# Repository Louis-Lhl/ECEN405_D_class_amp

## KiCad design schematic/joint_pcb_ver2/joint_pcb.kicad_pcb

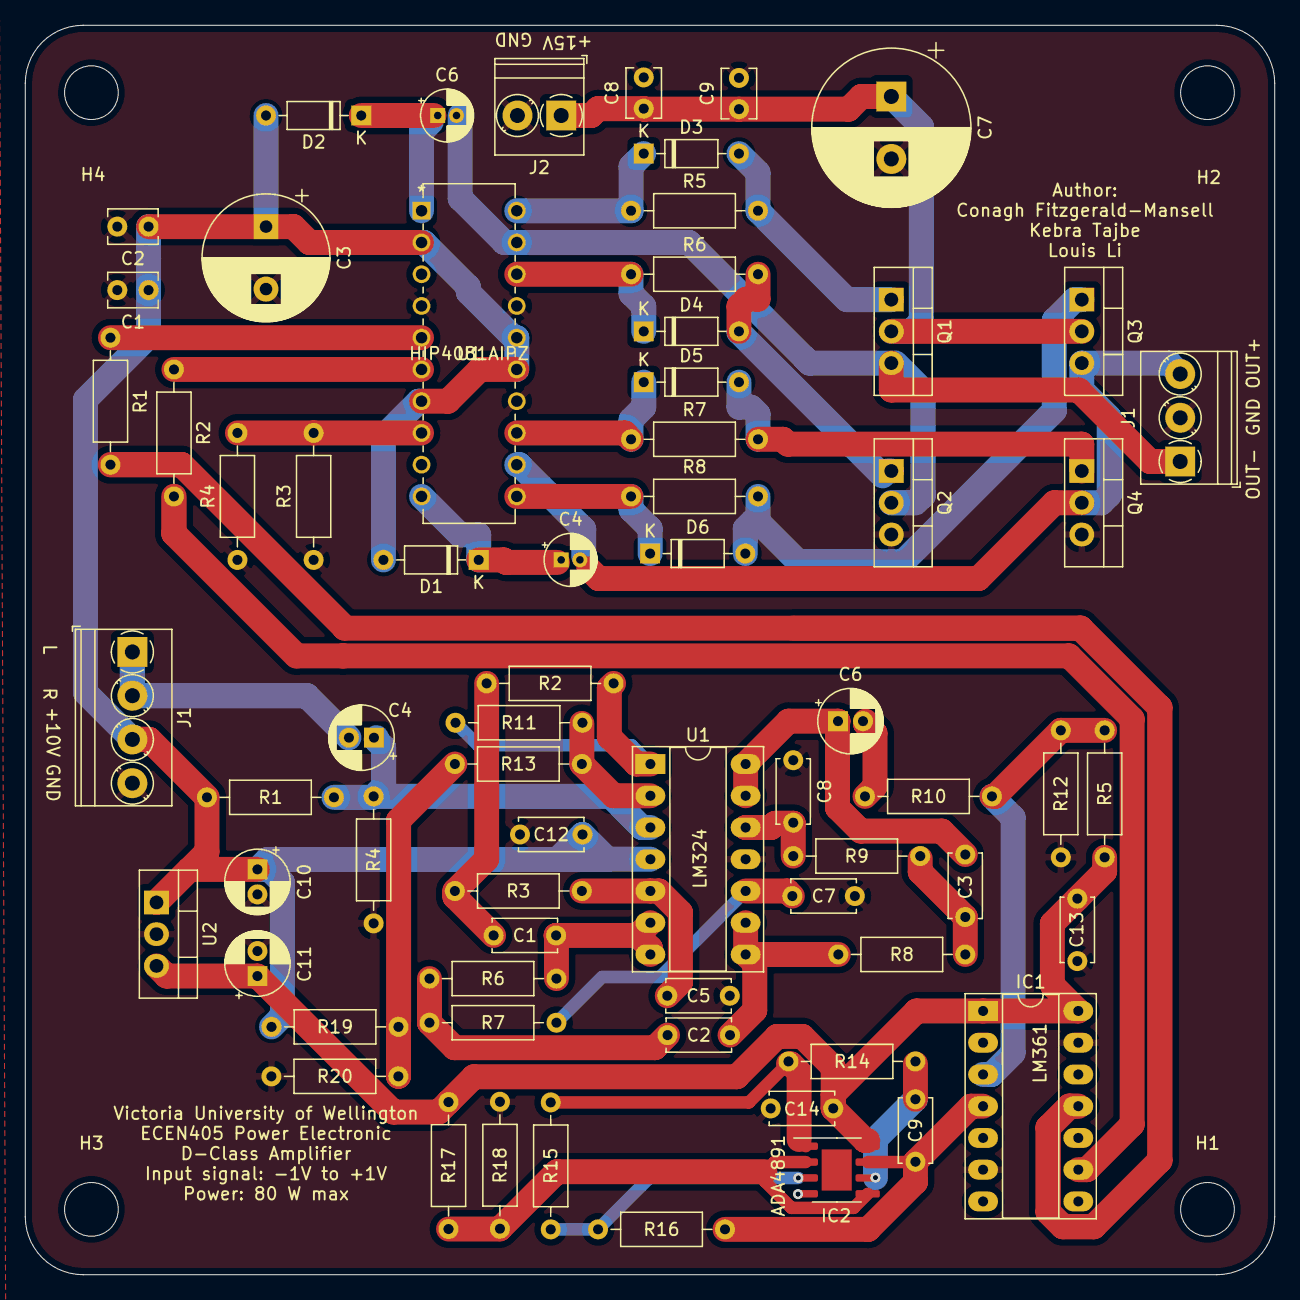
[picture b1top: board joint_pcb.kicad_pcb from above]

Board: 2 copper layers, 100.0 x 100.0 mm, 72 parts (0 on the bottom side), 41 nets.

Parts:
C1: 47n; C_Disc_D5.0mm_W2.5mm_P5.00mm
C1#2, C8#2: 10uF; C_Disc_D3.8mm_W2.6mm_P2.50mm
C2, C3: 56n; C_Disc_D5.0mm_W2.5mm_P5.00mm
C2#2, C9#2: 0.1uF; C_Disc_D3.8mm_W2.6mm_P2.50mm
C3#2: 100uF; CP_Radial_D10.0mm_P5.00mm
C4, C6: 100u; CP_Radial_D5.0mm_P2.00mm
C4#2, C6#2: 1uF; CP_Radial_D4.0mm_P1.50mm
C5, C9: 4.7n; C_Disc_D5.0mm_W2.5mm_P5.00mm
C7, C8: 5.6n; C_Disc_D5.0mm_W2.5mm_P5.00mm
C7#2: 1000uF; CP_Radial_D12.5mm_P5.00mm
C10, C11: 10u; CP_Radial_D5.0mm_P2.00mm
C12, C13, C14: 100nF; C_Disc_D5.0mm_W2.5mm_P5.00mm
D1, D2, D3, D4, D5, D6: 1N4148; D_DO-35_SOD27_P7.62mm_Horizontal
H1, H2, H3, H4: MountingHole; MountingHole_4.3mm_M4
IC1: LM361N_NOPB; DIP-14_W7.62mm_Socket_LongPads
IC2: ADA4891-2ARMZ-R7; SOIC-8-1EP_3.9x4.9mm_P1.27mm_EP2.41x3.3mm
J1: Screw_Terminal_01x04; TerminalBlock_Phoenix_PT-1,5-4-3.5-H_1x04_P3.50mm_Horizontal
J1#2: Power_PWM_output; TerminalBlock_Phoenix_PT-1,5-3-3.5-H_1x03_P3.50mm_Horizontal
J2: Amp_power; TerminalBlock_Phoenix_PT-1,5-2-3.5-H_1x02_P3.50mm_Horizontal
Q1, Q2, Q3, Q4: IRF510PBF; TO-220-3_Vertical
R1, R5, R10, R12, R15, R17, R18, R19: 10k; R_Axial_DIN0207_L6.3mm_D2.5mm_P10.16mm_Horizontal
R1#2, R2#2: 470R; R_Axial_DIN0207_L6.3mm_D2.5mm_P10.16mm_Horizontal
R2, R13: 1.2k; R_Axial_DIN0207_L6.3mm_D2.5mm_P10.16mm_Horizontal
R3, R16: 8.2k; R_Axial_DIN0207_L6.3mm_D2.5mm_P10.16mm_Horizontal
R3#2, R4#2: 47kR; R_Axial_DIN0207_L6.3mm_D2.5mm_P10.16mm_Horizontal
R4, R14, R20: 1k; R_Axial_DIN0207_L6.3mm_D2.5mm_P10.16mm_Horizontal
R5#2, R6#2, R7#2, R8#2: 100R; R_Axial_DIN0207_L6.3mm_D2.5mm_P10.16mm_Horizontal
R6: 680; R_Axial_DIN0207_L6.3mm_D2.5mm_P10.16mm_Horizontal
R7: 15k; R_Axial_DIN0207_L6.3mm_D2.5mm_P10.16mm_Horizontal
R8: 560; R_Axial_DIN0207_L6.3mm_D2.5mm_P10.16mm_Horizontal
R9: 18k; R_Axial_DIN0207_L6.3mm_D2.5mm_P10.16mm_Horizontal
R11: 5.6k; R_Axial_DIN0207_L6.3mm_D2.5mm_P10.16mm_Horizontal
U1: LM324; DIP-14_W7.62mm_Socket_LongPads
U1#2: HIP4081AIPZ
U2: LM7805_TO220; TO-220-3_Vertical

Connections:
+5V: C11.1, C13.1, C14.1, IC1.1, IC1.14, IC2.8, R5.1, R17.1, U2.3
+15V: C7#2.1, C8#2.1, C9#2.1, J2.1, Q1.2, Q3.2
AHO: D6.1, R8#2.1, U1#2.11
AHS: C4#2.2, J1#2.3, Q3.3, Q4.2, U1#2.12
ALO: D5.1, R7#2.1, U1#2.13
BHO: D3.1, R5#2.1, U1#2.20
BHS: C6#2.2, J1#2.1, Q1.3, Q2.2, U1#2.19
BLO: D4.1, R6#2.1, U1#2.18
Bias: R13.1, R19.2, R20.1
GND: C1#2.2, C2#2.2, C3#2.2, C5.2, C7.1, C7#2.2, C8.1, C8#2.2, C9#2.2, C10.2, C11.2, C12.2, C13.2, C14.2, IC1.6, IC1.8, IC1.10, IC1.13, IC2.4, J1.4, J1#2.2, J2.2, Q2.3, Q4.3, R3#2.1, R4.2, R4#2.1, R12.2, R18.2, R20.2, U1.11, U1#2.4, U1#2.14, U1#2.17, U2.2
Input: C4.2, J1.1, J1.2
unnamed: C1.1, R6.2, U1.6, U1.7
unnamed: C1.2, R2.1, R3.2
unnamed: C2.1, R6.1, R7.2
unnamed: C2.2, R8.2, U1.8, U1.9
unnamed: C3.1, C6.1, U1.13, U1.14
unnamed: C3.2, R8.1, R9.2
unnamed: C4.1, C4#2.1, D1.1, R1.2, R4.1, U1.3, U1#2.10
unnamed: C5.1, R3.1, U1.5
unnamed: C6#2.1, D2.1, U1#2.1
unnamed: C6.2, R10.1
unnamed: C7.2, R7.1, U1.10
unnamed: C8.2, R9.1, U1.12
unnamed: C9.1, IC1.4, IC2.7, R16.1
unnamed: C9.2, IC2.6, R14.1
unnamed: D3.2, Q1.1, R5#2.2
unnamed: D4.2, Q2.1, R6#2.2
unnamed: D5.2, Q4.1, R7#2.2
unnamed: D6.2, Q3.1, R8#2.2
unnamed: IC2.1, R14.2, R15.2
unnamed: IC2.3, R15.1, R16.2
unnamed: R1#2.1, U1#2.5
unnamed: R2#2.1, U1#2.6
unnamed: R3#2.2, R4#2.2, U1#2.8
unnamed: R2.2, R11.1, U1.1
unnamed: R11.2, R13.2, U1.2
PWM+: IC1.11, R1#2.2
PWM-: IC1.9, R2#2.2
Vcc: C1#2.1, C2#2.1, C3#2.1, C10.1, C12.1, D1.2, D2.2, J1.3, R1.1, R19.1, U1.4, U1#2.2, U1#2.7, U1#2.15, U1#2.16, U2.1
Vref: IC2.2, IC2.5, R17.2, R18.1
filterOut: IC1.3, R5.2, R10.2, R12.1

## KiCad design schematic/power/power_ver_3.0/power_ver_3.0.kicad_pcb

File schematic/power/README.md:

# Schematic

This folder contains the schematic and PCB layout files and the PCB Gerber files of the power amplifier. These were created using [Kicad](https://www.kicad.org/).

* The PCB Gerbers is [here]().
* The BOM is [here](power_ver_2.0/power_ver_2.0.csv).

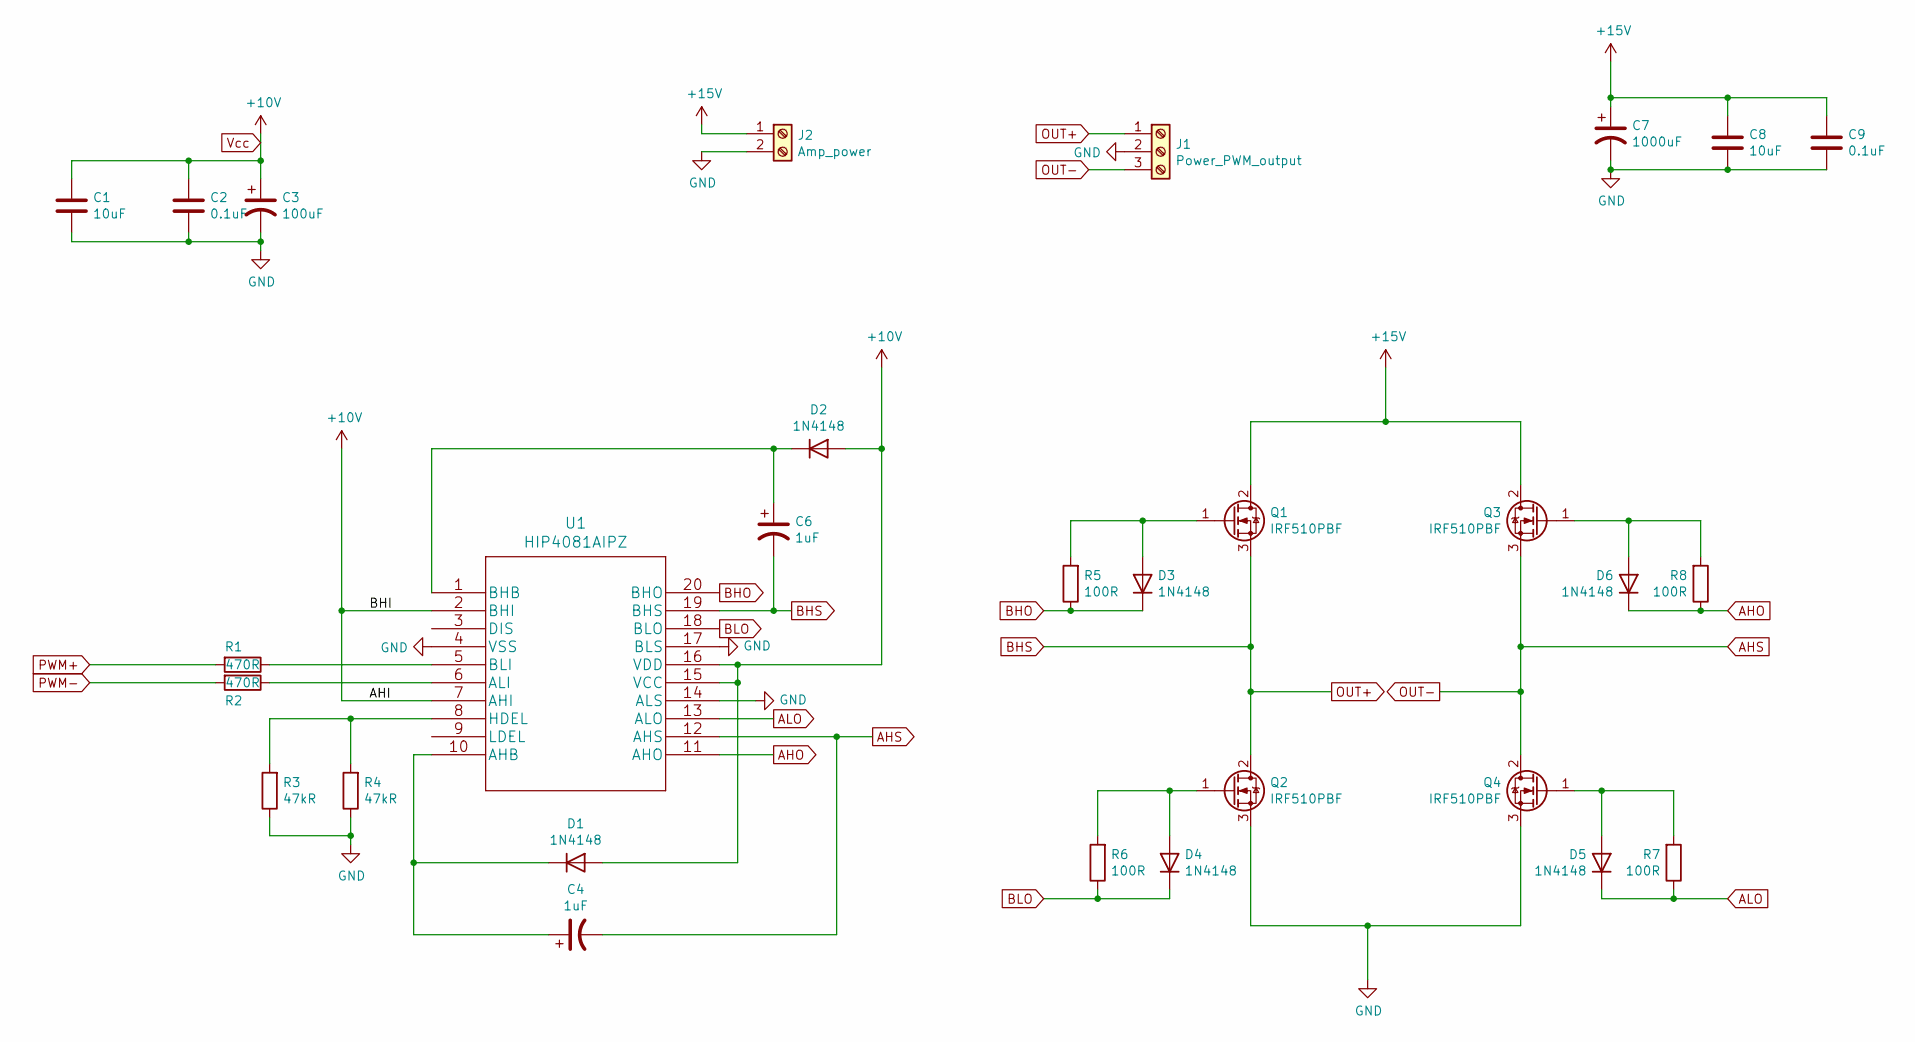
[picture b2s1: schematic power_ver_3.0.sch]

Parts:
C1, C8: 10uF; C_Disc_D3.8mm_W2.6mm_P2.50mm; MPN C324C106K3R5TA
C2, C9: 0.1uF; C_Disc_D3.8mm_W2.6mm_P2.50mm; MPN K104Z15Y5VE5TL2
C3: 100uF; CP_Radial_D10.0mm_P5.00mm; MPN ECE-A1HN101U
C4, C6: 1uF; CP_Radial_D4.0mm_P1.50mm; MPN ESS105M050AB2EA
C7: 1000uF; CP_Radial_D12.5mm_P5.00mm; MPN EEU-FC1H102L
D1, D2, D3, D4, D5, D6: 1N4148; D_DO-35_SOD27_P7.62mm_Horizontal; MPN 1N4148
J1: Power_PWM_output; TerminalBlock_Phoenix_PT-1,5-3-3.5-H_1x03_P3.50mm_Horizontal
J2: Amp_power; TerminalBlock_Phoenix_PT-1,5-2-3.5-H_1x02_P3.50mm_Horizontal
Q1, Q2, Q3, Q4: IRF510PBF; TO-220-3_Vertical
R1, R2: 470R; R_Axial_DIN0207_L6.3mm_D2.5mm_P10.16mm_Horizontal; MPN CFR-25JB-52-470R
R3, R4: 47kR; R_Axial_DIN0207_L6.3mm_D2.5mm_P10.16mm_Horizontal
R5, R6, R7, R8: 100R; R_Axial_DIN0207_L6.3mm_D2.5mm_P10.16mm_Horizontal; MPN CFR-25JR-52-100R
U1: HIP4081AIPZ

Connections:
+15V: C7.1, C8.1, C9.1, J2.1, Q1.2 (D), Q3.2 (D)
AHO: D6.1 (K), R8.1, U1.11 (AHO)
AHS: C4.2, J1.3, Q3.3 (S), Q4.2 (D), U1.12 (AHS)
ALO: D5.1 (K), R7.1, U1.13 (ALO)
BHO: D3.1 (K), R5.1, U1.20 (BHO)
BHS: C6.2, J1.1, Q1.3 (S), Q2.2 (D), U1.19 (BHS)
BLO: D4.1 (K), R6.1, U1.18 (BLO)
GND: C1.2, C2.2, C3.2, C7.2, C8.2, C9.2, J1.2, J2.2, Q2.3 (S), Q4.3 (S), R3.1, R4.1, U1.4 (VSS), U1.14 (ALS), U1.17 (BLS)
unnamed: C4.1, D1.1 (K), U1.10 (AHB)
unnamed: C6.1, D2.1 (K), U1.1 (BHB)
unnamed: D3.2 (A), Q1.1 (G), R5.2
unnamed: D4.2 (A), Q2.1 (G), R6.2
unnamed: D5.2 (A), Q4.1 (G), R7.2
unnamed: D6.2 (A), Q3.1 (G), R8.2
unnamed: R1.1, U1.5 (BLI)
unnamed: R2.1, U1.6 (ALI)
unnamed: R3.2, R4.2, U1.8 (HDEL)
PWM+: R1.2
PWM-: R2.2
Vcc: C1.1, C2.1, C3.1, D1.2 (A), D2.2 (A), U1.2 (BHI), U1.7 (AHI), U1.15 (VCC), U1.16 (VDD)

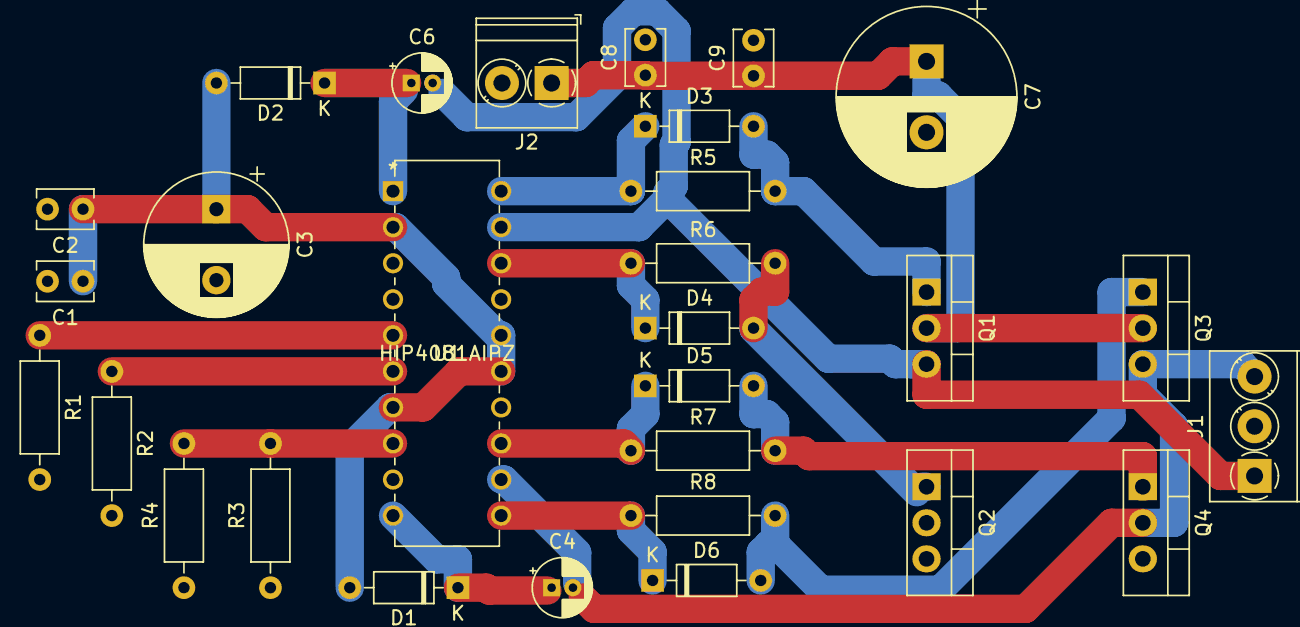
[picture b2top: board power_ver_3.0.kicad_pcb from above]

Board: 2 copper layers, 29 parts (0 on the bottom side), 18 nets.

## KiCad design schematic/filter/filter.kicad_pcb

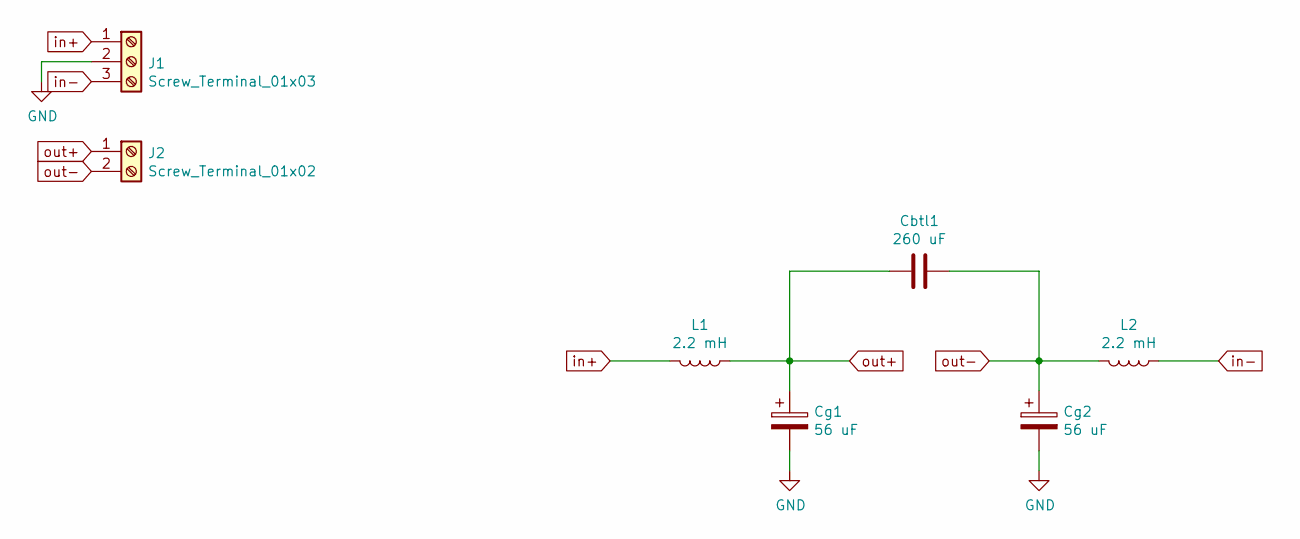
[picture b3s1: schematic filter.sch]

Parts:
Cbtl1: 260 uF; C_Radial_D50.00mm_P16.00mm_P37.50mm
Cg1, Cg2: 56 uF; C_Radial_D6.3mm_H11.0mm_P2.50mm
J1: Screw_Terminal_01x03; TerminalBlock_Phoenix_PT-1,5-3-3.5-H_1x03_P3.50mm_Horizontal
J2: Screw_Terminal_01x02; TerminalBlock_Phoenix_PT-1,5-2-3.5-H_1x02_P3.50mm_Horizontal
L1, L2: 2.2 mH; L_Radial_D40.6mm_P27.94mm_Vishay_IHB-4

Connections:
GND: Cg1.2, Cg2.2, J1.2
in+: J1.1, L1.2
in-: J1.3, L2.1
out+: Cbtl1.2, Cg1.1, J2.1, L1.1
out-: Cbtl1.1, Cg2.1, J2.2, L2.2

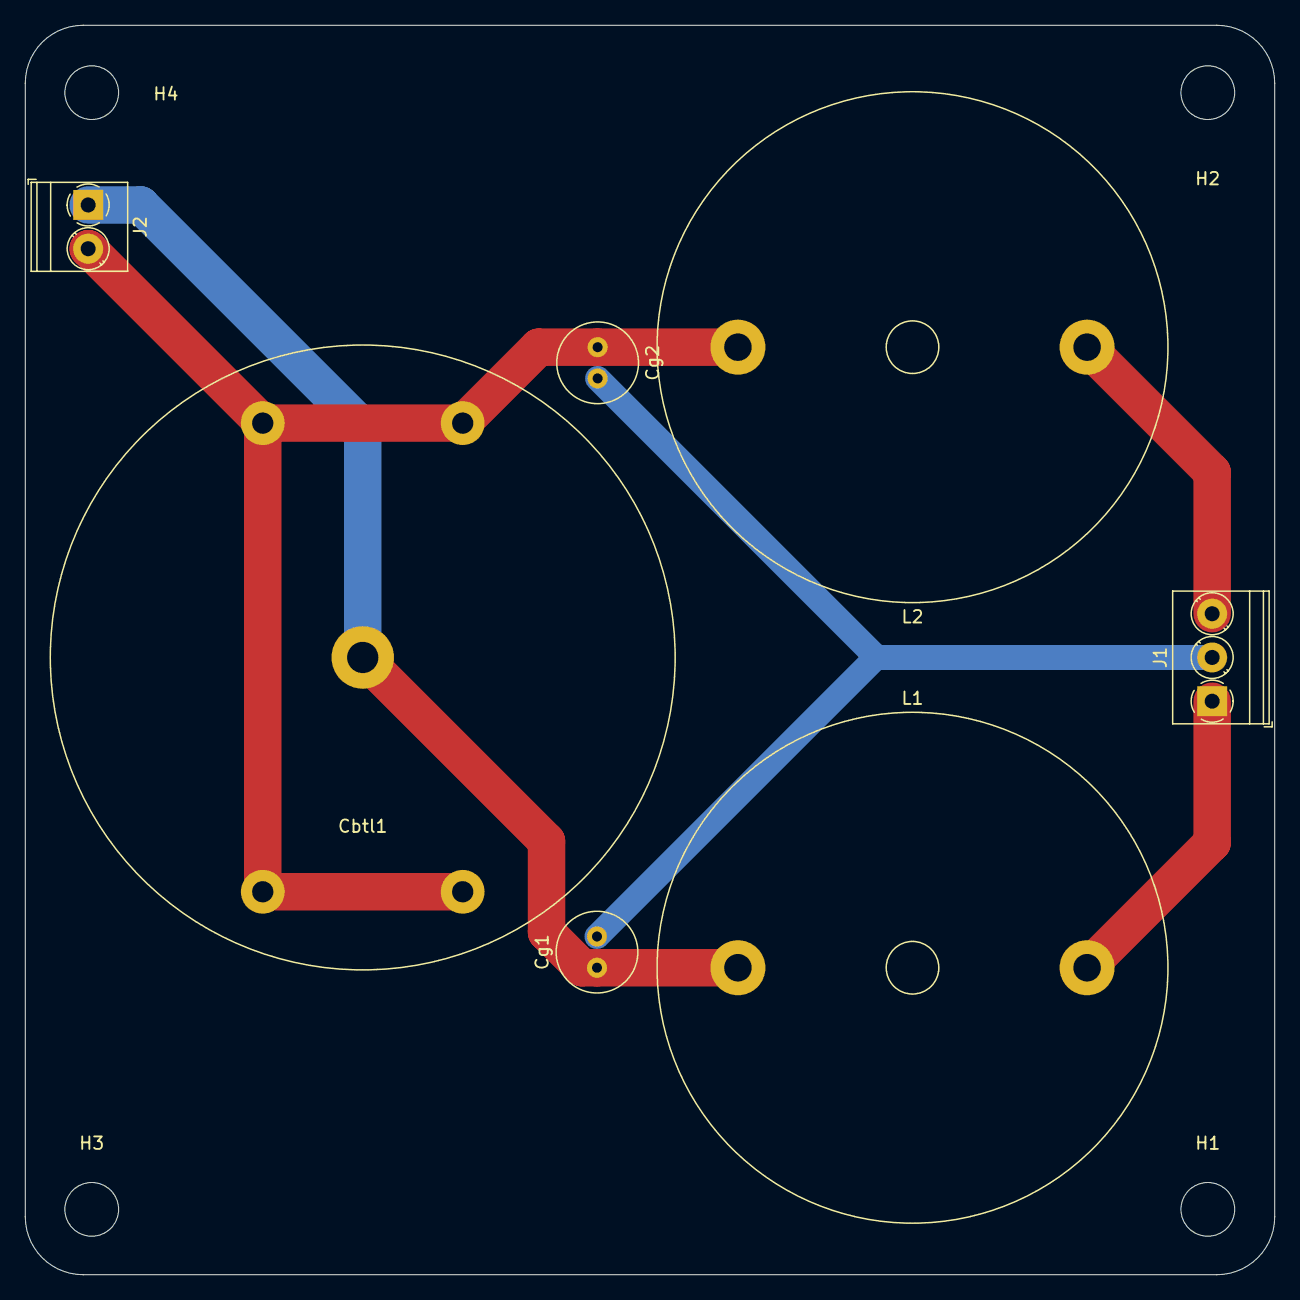
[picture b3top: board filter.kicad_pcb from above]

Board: 2 copper layers, 100.0 x 100.0 mm, 11 parts (0 on the bottom side), 5 nets.

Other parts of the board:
H1, H2, H3, H4: MountingHole; MountingHole_4.3mm_M4

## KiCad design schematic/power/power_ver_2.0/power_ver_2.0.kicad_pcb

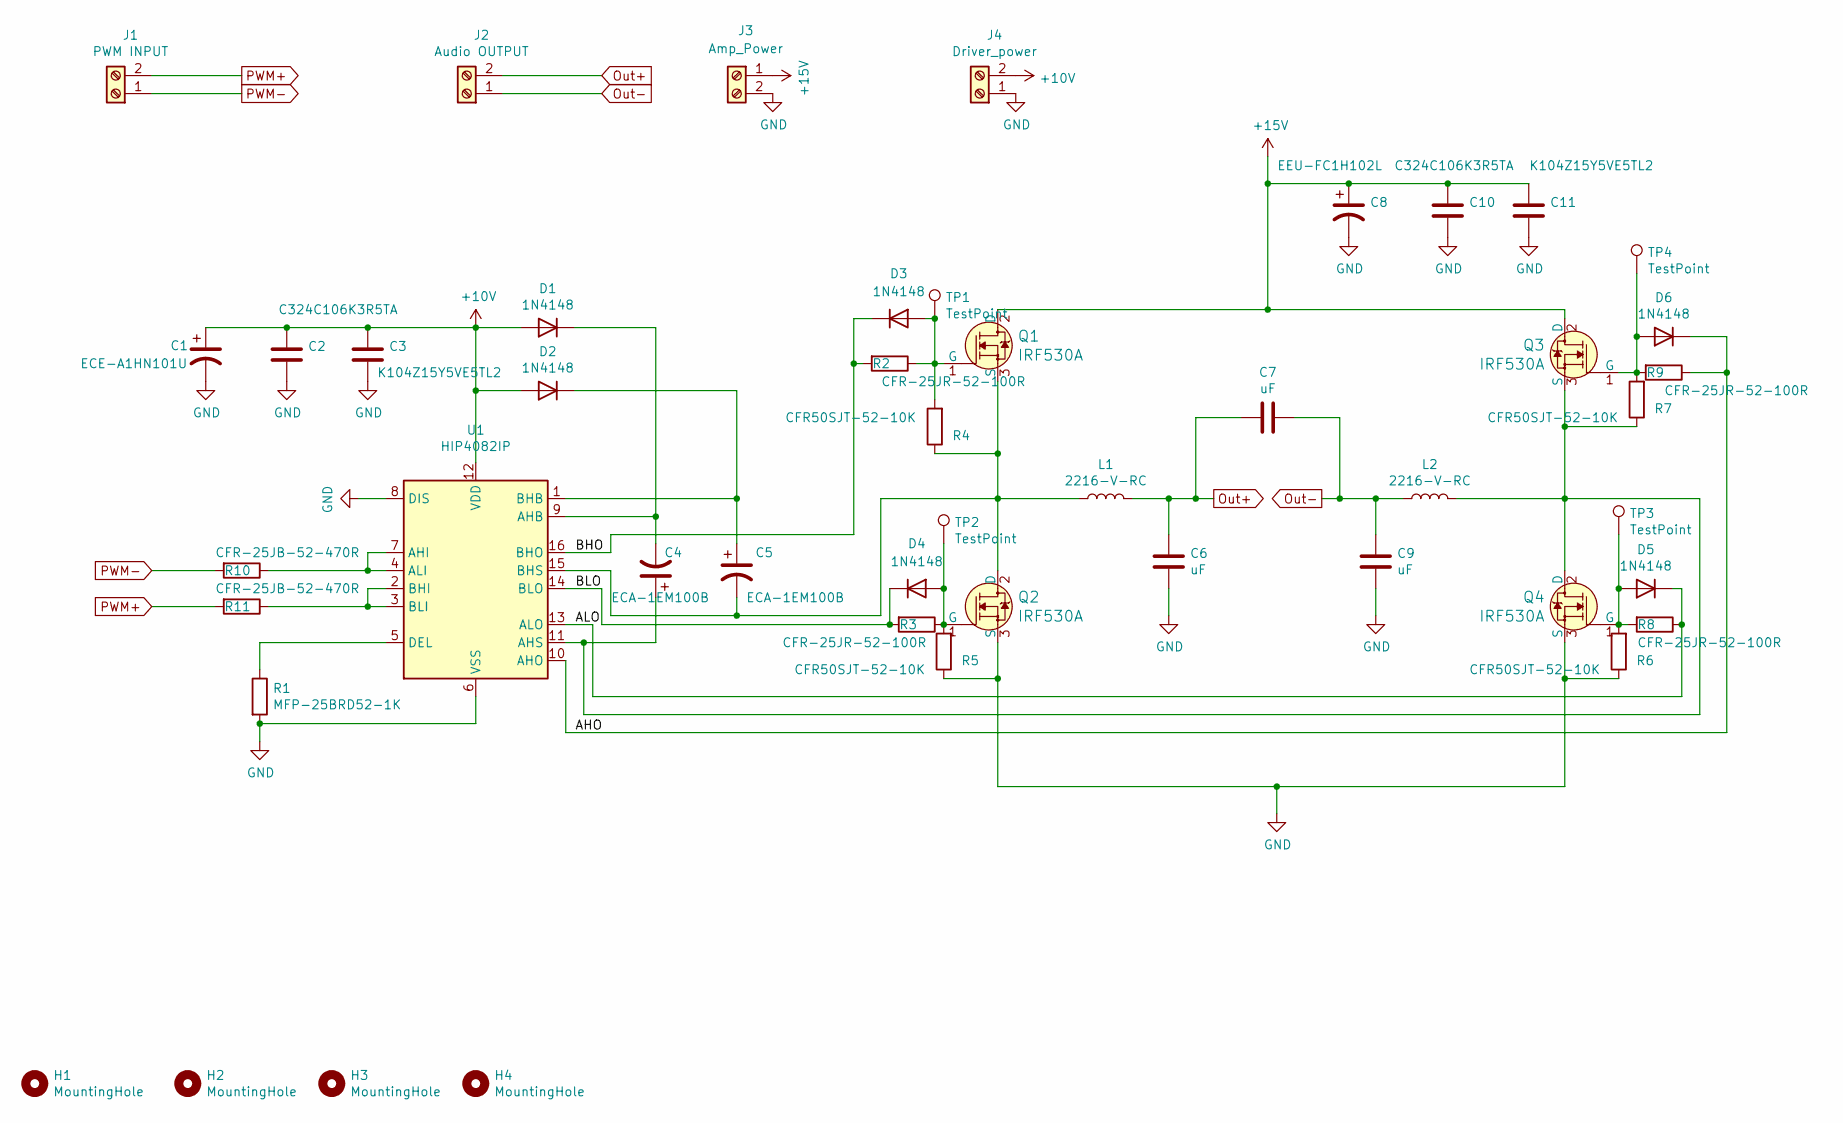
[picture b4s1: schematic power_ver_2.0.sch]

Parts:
C1: ECE-A1HN101U; CP_Radial_D10.0mm_P5.00mm
C2, C10: C324C106K3R5TA; C_Disc_D3.8mm_W2.6mm_P2.50mm
C3, C11: K104Z15Y5VE5TL2; C_Disc_D3.8mm_W2.6mm_P2.50mm
C4, C5: ECA-1EM100B; CP_Radial_Tantal_D5.0mm_P5.00mm
C6, C7, C9: uF; C_Radial_D10.0mm_H12.5mm_P5.00mm
C8: EEU-FC1H102L; CP_Radial_D12.5mm_P5.00mm
D1, D2, D3, D4, D5, D6: 1N4148; D_DO-35_SOD27_P7.62mm_Horizontal; Digi-Key_PN 1N4148FS-ND
H1, H2, H3, H4: MountingHole; MountingHole_4.3mm_M4
J1: PWM INPUT; TerminalBlock_Altech_AK300-2_P5.00mm; Digi-Key_PN 277-1667-ND
J2: Audio OUTPUT; TerminalBlock_Altech_AK300-2_P5.00mm; Digi-Key_PN 277-1667-ND
J3: Amp_Power; TerminalBlock_Altech_AK300-2_P5.00mm; Digi-Key_PN 277-1667-ND
J4: Driver_power; TerminalBlock_Altech_AK300-2_P5.00mm; Digi-Key_PN 277-1667-ND
L1, L2: 2216-V-RC; L_Toroid_Vertical_L24.6mm_W15.5mm_P11.44mm_Pulse_KM-4
Q1, Q2, Q3, Q4: IRF530A; TO-220-3; MPN IRF530A; Digi-Key_PN 2156-IRF530A-ND
R1: MFP-25BRD52-1K; R_Axial_DIN0207_L6.3mm_D2.5mm_P10.16mm_Horizontal
R2, R3, R8, R9: CFR-25JR-52-100R; R_Axial_DIN0207_L6.3mm_D2.5mm_P10.16mm_Horizontal
R4, R5, R6, R7: CFR50SJT-52-10K; R_Axial_DIN0207_L6.3mm_D2.5mm_P10.16mm_Horizontal
R10, R11: CFR-25JB-52-470R; R_Axial_DIN0207_L6.3mm_D2.5mm_P10.16mm_Horizontal
TP1, TP2, TP3, TP4: TestPoint; TestPoint_THTPad_D2.0mm_Drill1.0mm
U1: HIP4082IP; DIP-16_W7.62mm

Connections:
+10V: C1.1, C2.1, C3.1, D1.2 (A), D2.2 (A), J4.2, U1.12 (VDD)
+15V: C8.1, C10.1, C11.1, J3.1, Q1.2 (D), Q3.2 (D)
/AHO: D6.1 (K), R9.1, U1.10 (AHO)
/ALO: D5.1 (K), R8.1, U1.13 (ALO)
/BHO: D3.1 (K), R2.2, U1.16 (BHO)
/BLO: D4.1 (K), R3.2, U1.14 (BLO)
GND: C1.2, C2.2, C3.2, C6.2, C8.2, C9.2, C10.2, C11.2, J3.2, J4.1, Q2.3 (S), Q4.3 (S), R1.2, R5.1, R6.1, U1.6 (VSS), U1.8 (DIS)
unnamed: C4.1, L2.2, Q3.3 (S), Q4.2 (D), R7.1, U1.11 (AHS)
unnamed: C4.2, D1.1 (K), U1.9 (AHB)
unnamed: C5.1, D2.1 (K), U1.1 (BHB)
unnamed: C5.2, L1.1, Q1.3 (S), Q2.2 (D), R4.1, U1.15 (BHS)
unnamed: D3.2 (A), Q1.1 (G), R2.1, R4.2, TP1.1
unnamed: D4.2 (A), Q2.1 (G), R3.1, R5.2, TP2.1
unnamed: D5.2 (A), Q4.1 (G), R6.2, R8.2, TP3.1
unnamed: D6.2 (A), Q3.1 (G), R7.2, R9.2, TP4.1
unnamed: R1.1, U1.5 (DEL)
unnamed: R10.1, U1.4 (ALI), U1.7 (AHI)
unnamed: R11.1, U1.2 (BHI), U1.3 (BLI)
Out+: C6.1, C7.2, J2.2, L1.2
Out-: C7.1, C9.1, J2.1, L2.1
PWM+: J1.2, R11.2
PWM-: J1.1, R10.2

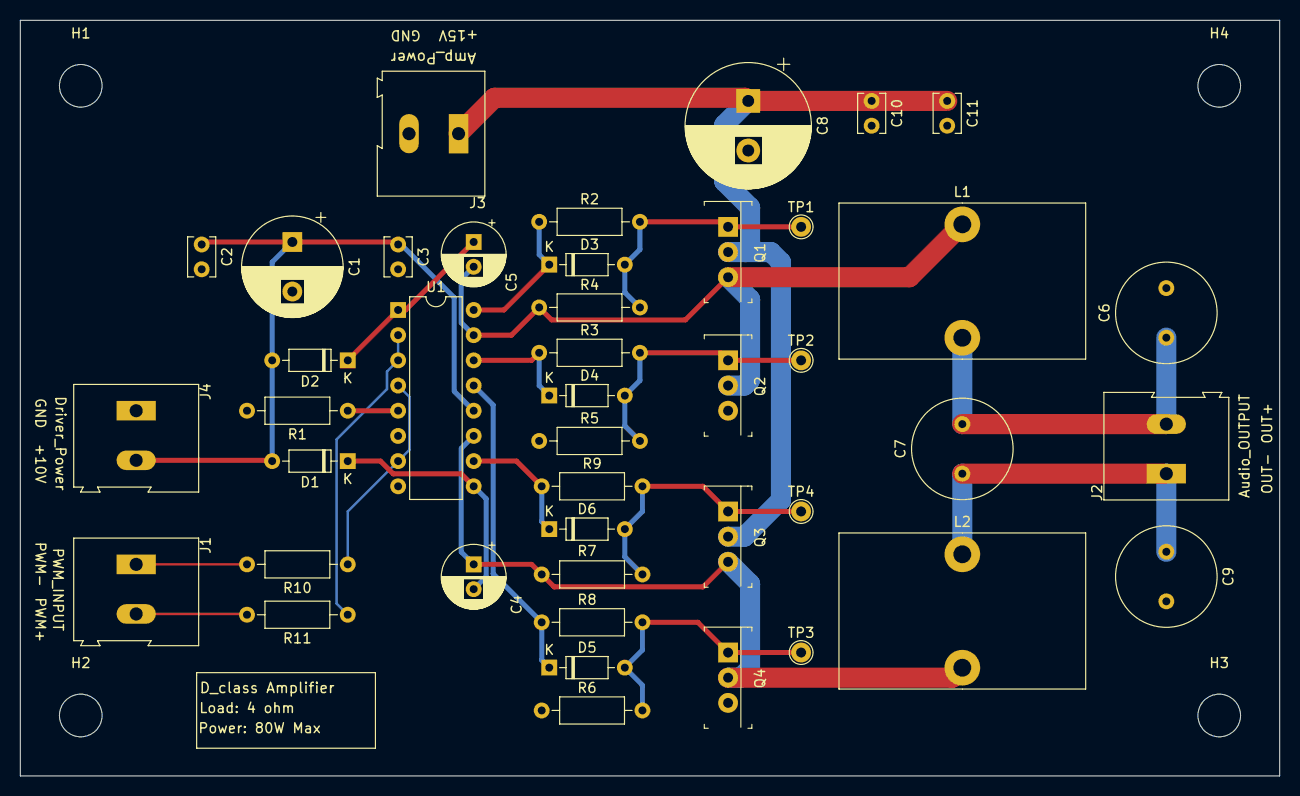
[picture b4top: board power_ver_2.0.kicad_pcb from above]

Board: 2 copper layers, 127.0 x 76.2 mm, 47 parts (0 on the bottom side), 22 nets.

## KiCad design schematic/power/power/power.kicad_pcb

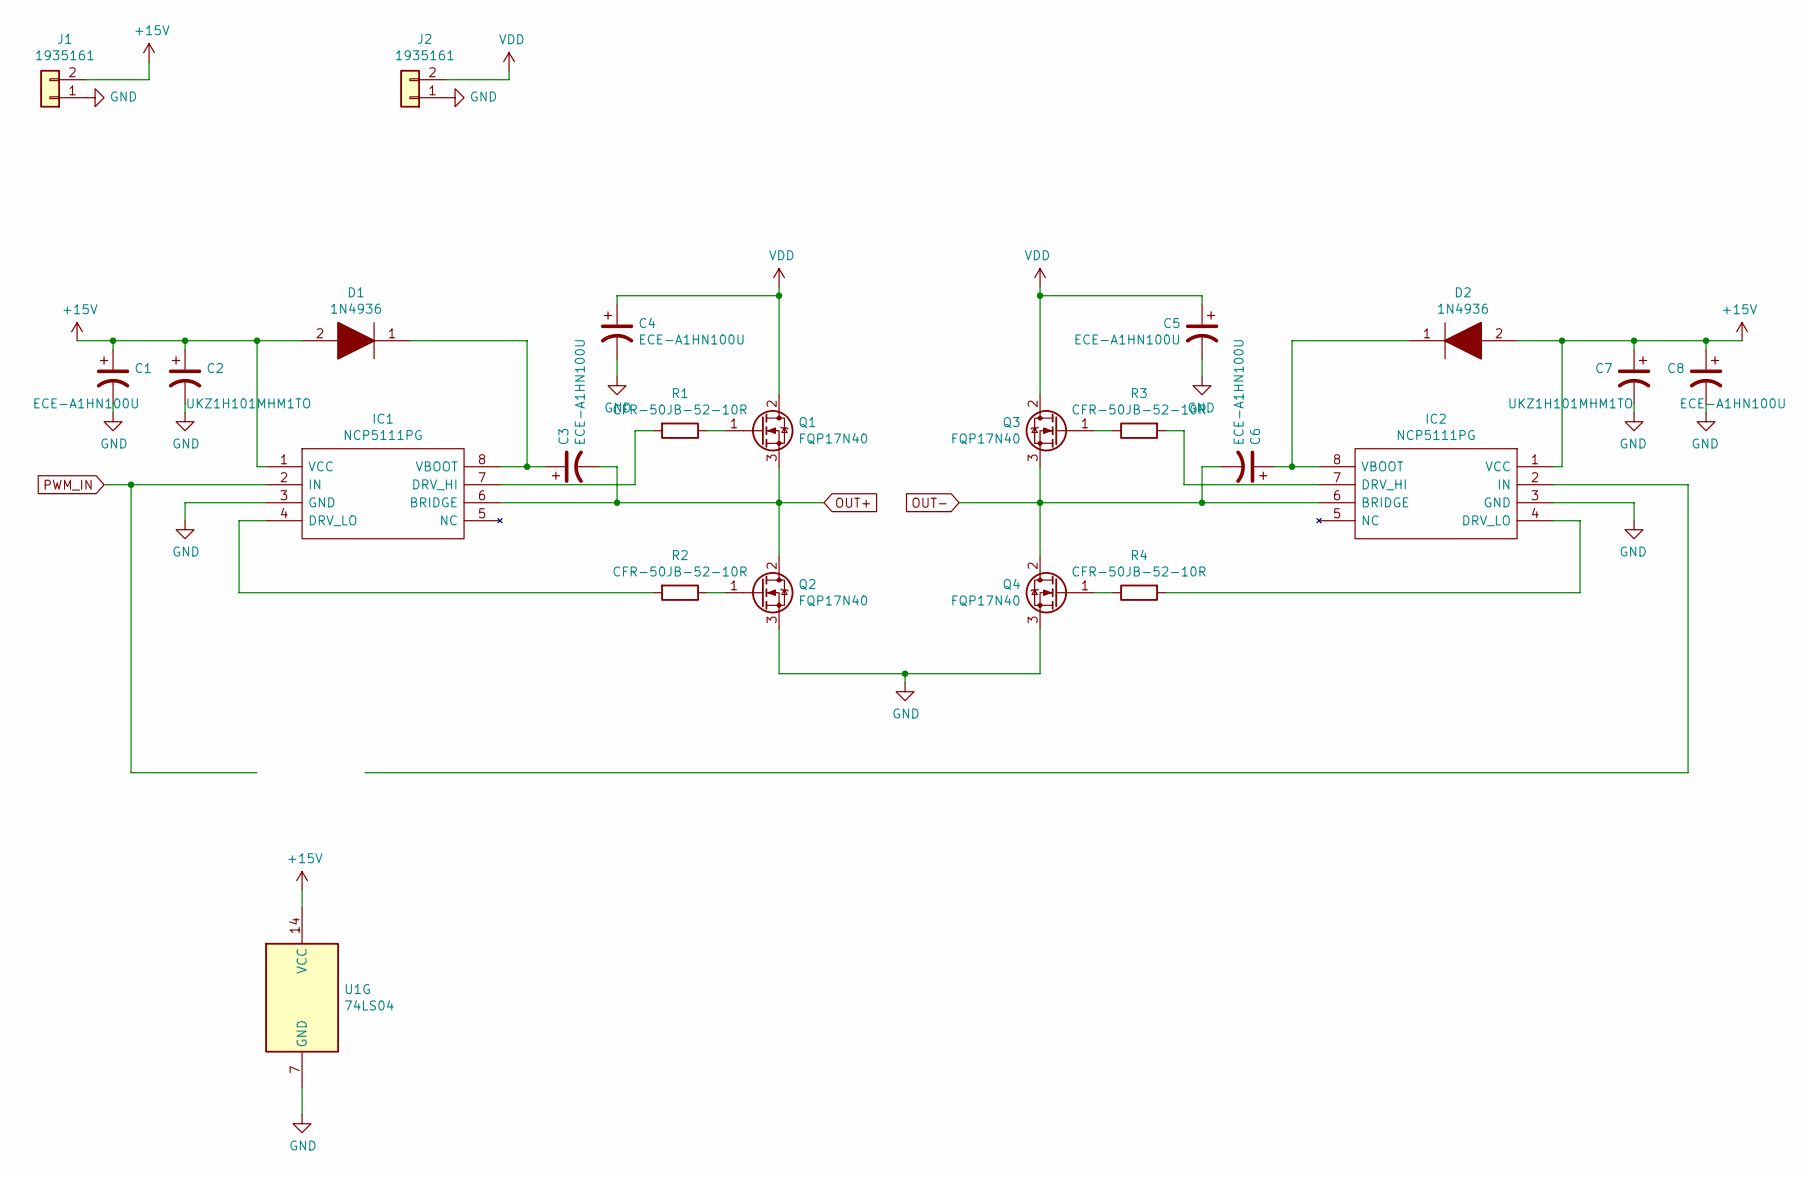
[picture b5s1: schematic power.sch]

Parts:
C1, C3, C4, C5, C6, C8: ECE-A1HN100U; CP_Radial_D6.3mm_P2.50mm
C2, C7: UKZ1H101MHM1TO; CP_Radial_D12.5mm_P5.00mm
D1, D2: 1N4936; DIOAD1405W86L465D235; Manufacturer_Part_Number 1N4936; Mouser Part Number 512-1N4936
IC1, IC2: NCP5111PG; DIP794W56P254L959H533Q8N; Manufacturer_Part_Number NCP5111PG; Mouser Part Number 863-NCP5111PG
J1, J2: 1935161; TerminalBlock_Altech_AK300-2_P5.00mm
Q1, Q2, Q3, Q4: FQP17N40; TO254P470X990X1910-3P
R1, R2, R3, R4: CFR-50JB-52-10R; R_Axial_DIN0309_L9.0mm_D3.2mm_P12.70mm_Horizontal
U1: 74LS04; DIP-14_W7.62mm

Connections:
+15V: C1.1, C2.1, C7.1, C8.1, D1.2, D2.2, IC1.1 (VCC), IC2.1 (VCC), J1.2, U1.14 (VCC)
GND: C1.2, C2.2, C4.2, C5.2, C7.2, C8.2, IC1.3 (GND), IC2.3 (GND), J1.1, J2.1, Q2.3 (S), Q4.3 (S), U1.7 (GND)
unnamed: C3.1, D1.1, IC1.8 (VBOOT)
unnamed: C6.1, D2.1, IC2.8 (VBOOT)
unnamed: IC1.4 (DRV_LO), R2.2
unnamed: IC1.7 (DRV_HI), R1.2
unnamed: IC2.2 (IN), U1.12
unnamed: IC2.4 (DRV_LO), R4.2
unnamed: IC2.7 (DRV_HI), R3.2
unnamed: Q1.1 (G), R1.1
unnamed: Q2.1 (G), R2.1
unnamed: Q3.1 (G), R3.1
unnamed: Q4.1 (G), R4.1
OUT+: C3.2, IC1.6 (BRIDGE), Q1.3 (S), Q2.2 (D)
OUT-: C6.2, IC2.6 (BRIDGE), Q3.3 (S), Q4.2 (D)
PWM_IN: IC1.2 (IN), U1.13
VDD: C4.1, C5.1, J2.2, Q1.2 (D), Q3.2 (D)

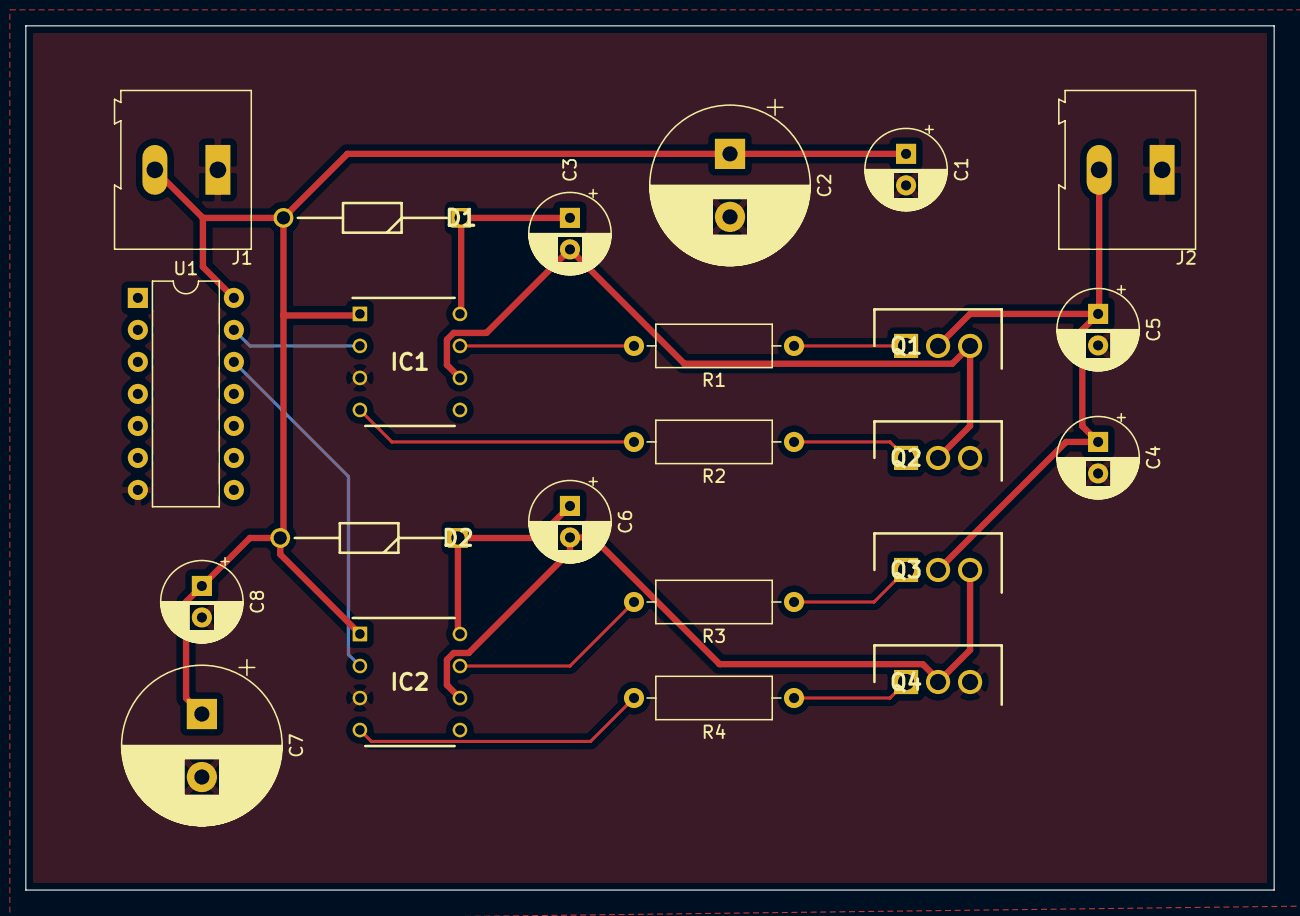
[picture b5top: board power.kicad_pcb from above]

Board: 2 copper layers, 99.1 x 68.6 mm, 23 parts (0 on the bottom side), 17 nets.

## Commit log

2021-08-10 init repo
2021-08-19 full bridge amplifier schematic
2021-08-19 Added connectors and filter section
2021-08-19 Added input section
2021-08-20 assign part number to power schematic
2021-08-20 Added small decoupling caps
2021-08-20 Updated terminals and added IC labels
2021-08-20 initial PCB layout for power
2021-08-20 Terminal updates
2021-08-20 Added manufacture directory with readme
2021-08-31 add power ver 2
2021-08-31 ver2 pcb layout
2021-09-01 auto roulting
2021-09-02 finish pcb trace layout
2021-09-02 add mounting hole, test point
2021-09-02 labels
2021-09-02 add BOM
2021-09-02 add readme file
2021-09-02 add joint pcb proj
2021-09-02 Added spice model for output filter
2021-09-03 Added ADA4891 Symbol
2021-09-03 Added component calculation
2021-09-03 Updated simulation component values
2021-09-03 joint pcb power section
2021-09-03 add trace
2021-09-08 Fixed PCB
2021-09-09 Created filter section project
2021-09-09 Added film cap footprint
2021-09-09 Generated gerber files
2021-09-09 Added ground ouput, aligned mounting holes, rounded corners
2021-09-10 move geber files to manufacture folder and add BOM csv file
2021-09-10 updata readme for manufactring
2021-09-10 create a zip file
2021-09-13 power 3.0 schematic and pcb layout
2021-09-13 power 3.0 pcb layout
2021-09-13 finish layout for PCB
2021-09-13 connect up 10V
2021-09-13 add text and zoon
2021-09-13 update bom
2021-09-13 Reloaded project
2021-09-13 Removed thermal vias from ADA4981
2021-09-13 add manufacture zip
2021-11-02 Add power section scope measurement
2021-11-02 output filter results
2021-11-04 add description for power stage results
2021-11-04 Added full system results
2021-11-05 add input section scope view

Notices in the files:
parts and their libraries:
Copyright 2021 Accelerated Designs. All rights reserved.
